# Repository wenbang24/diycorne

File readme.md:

# 42corne

im too stubborn to buy a corne

* Keyboard Maintainer: [Ben Wang](https://github.com/DaPotato69)
* Hardware Supported: pro micro or any size that works

Make example for this keyboard (after setting up your build environment):

    make 42corne:default

Flashing example for this keyboard:

    make 42corne:default:flash

## Bootloader

Enter the bootloader in 3 ways:

press the reset button the the right side of the kb (im using sparkfun rp2040 pro micro, instructions vary for different microcontrollers)

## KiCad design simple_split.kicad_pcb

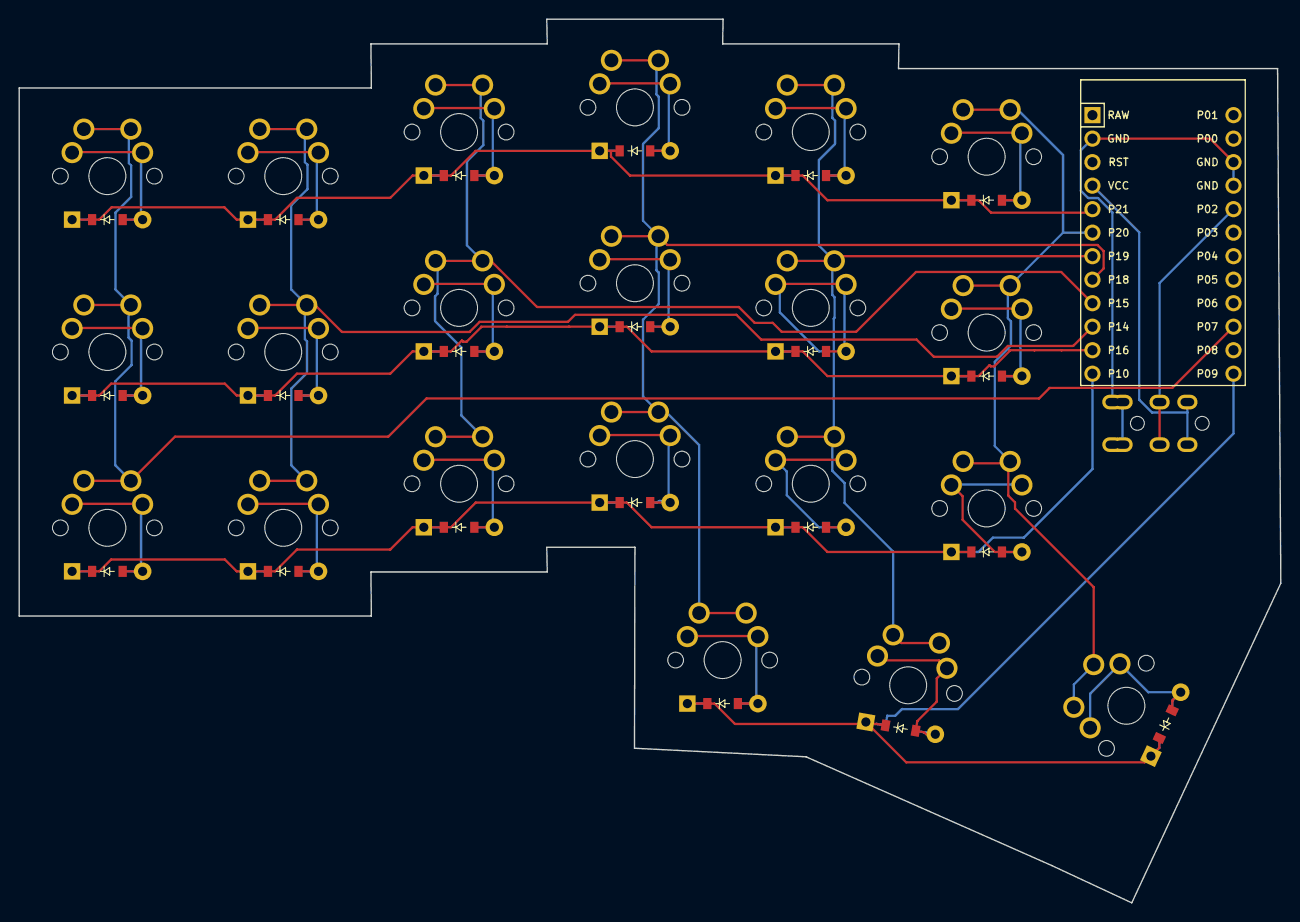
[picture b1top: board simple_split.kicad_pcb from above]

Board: 2 copper layers, 136.3 x 95.5 mm, 44 parts (0 on the bottom side), 34 nets.

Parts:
D1, D2, D3, D4, D5, D6, D7, D8, D9, D10, D11, D12, D13, D14, D15, D16, D17, D18, D19, D20, D21: ComboDiode
MCU1: ProMicro
S1, S2, S3, S4, S5, S6, S7, S8, S9, S10, S11, S12, S13, S14, S15, S16, S17, S18, S19, S20, S21: MX
TRRS1: TRRS-PJ-320A-dual

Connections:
GND: MCU1.2, MCU1.15, MCU1.16, TRRS1.1, TRRS1.2
P2: MCU1.17, TRRS1.3
P7: MCU1.22, S1.1, S2.1, S3.1
P9: D19.1, D20.1, D21.1, MCU1.24
P10: D1.1, D4.1, D7.1, D10.1, D13.1, D16.1, MCU1.12
P14: MCU1.10, S4.1, S5.1, S6.1
P15: MCU1.9, S7.1, S8.1, S9.1
P16: D2.1, D5.1, D8.1, D11.1, D14.1, D17.1, MCU1.11
P18: MCU1.8, S10.1, S11.1, S12.1, S19.1
P19: MCU1.7, S13.1, S14.1, S15.1, S20.1
P20: MCU1.6, S16.1, S17.1, S18.1, S21.1
P21: D3.1, D6.1, D9.1, D12.1, D15.1, D18.1, MCU1.5
VCC: MCU1.4, TRRS1.4
index_bottom: D13.2, S13.2
index_home: D14.2, S14.2
index_top: D15.2, S15.2
inner_bottom: D16.2, S16.2
inner_home: D17.2, S17.2
inner_top: D18.2, S18.2
middle_bottom: D10.2, S10.2
middle_home: D11.2, S11.2
middle_top: D12.2, S12.2
mod_bottom: D1.2, S1.2
mod_home: D2.2, S2.2
mod_top: D3.2, S3.2
pinky_bottom: D4.2, S4.2
pinky_home: D5.2, S5.2
pinky_top: D6.2, S6.2
reachy_home: D21.2, S21.2
ring_bottom: D7.2, S7.2
ring_home: D8.2, S8.2
ring_top: D9.2, S9.2
tuckier_home: D19.2, S19.2
tucky_home: D20.2, S20.2

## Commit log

2023-09-08 Create firmware folder
